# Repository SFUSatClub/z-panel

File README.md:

# Z Face Panel
KiCad project for the outside panel attached to the z faces of the cubesat. The panel contains a SMT GPS antenna and 4 sun sensors. The interface is a MCX jack for the GPS and a 14 pin ribbon cable for the sun sensor power and IO.

This repository uses the SFU Satellite Team's KiCad component library as a submodule.
To start working on the repository:

```
1. Open a git shell
2. Navigate to the directory you wish to place the repository inside
3. git clone --recursive "https://github.com/SFUSatClub/z-panel.git"
```

If you modify either the component schematic or footprint libraries you must push those changes to the SFUSatClub/KiCad-Lib repository, then commit the project repository.

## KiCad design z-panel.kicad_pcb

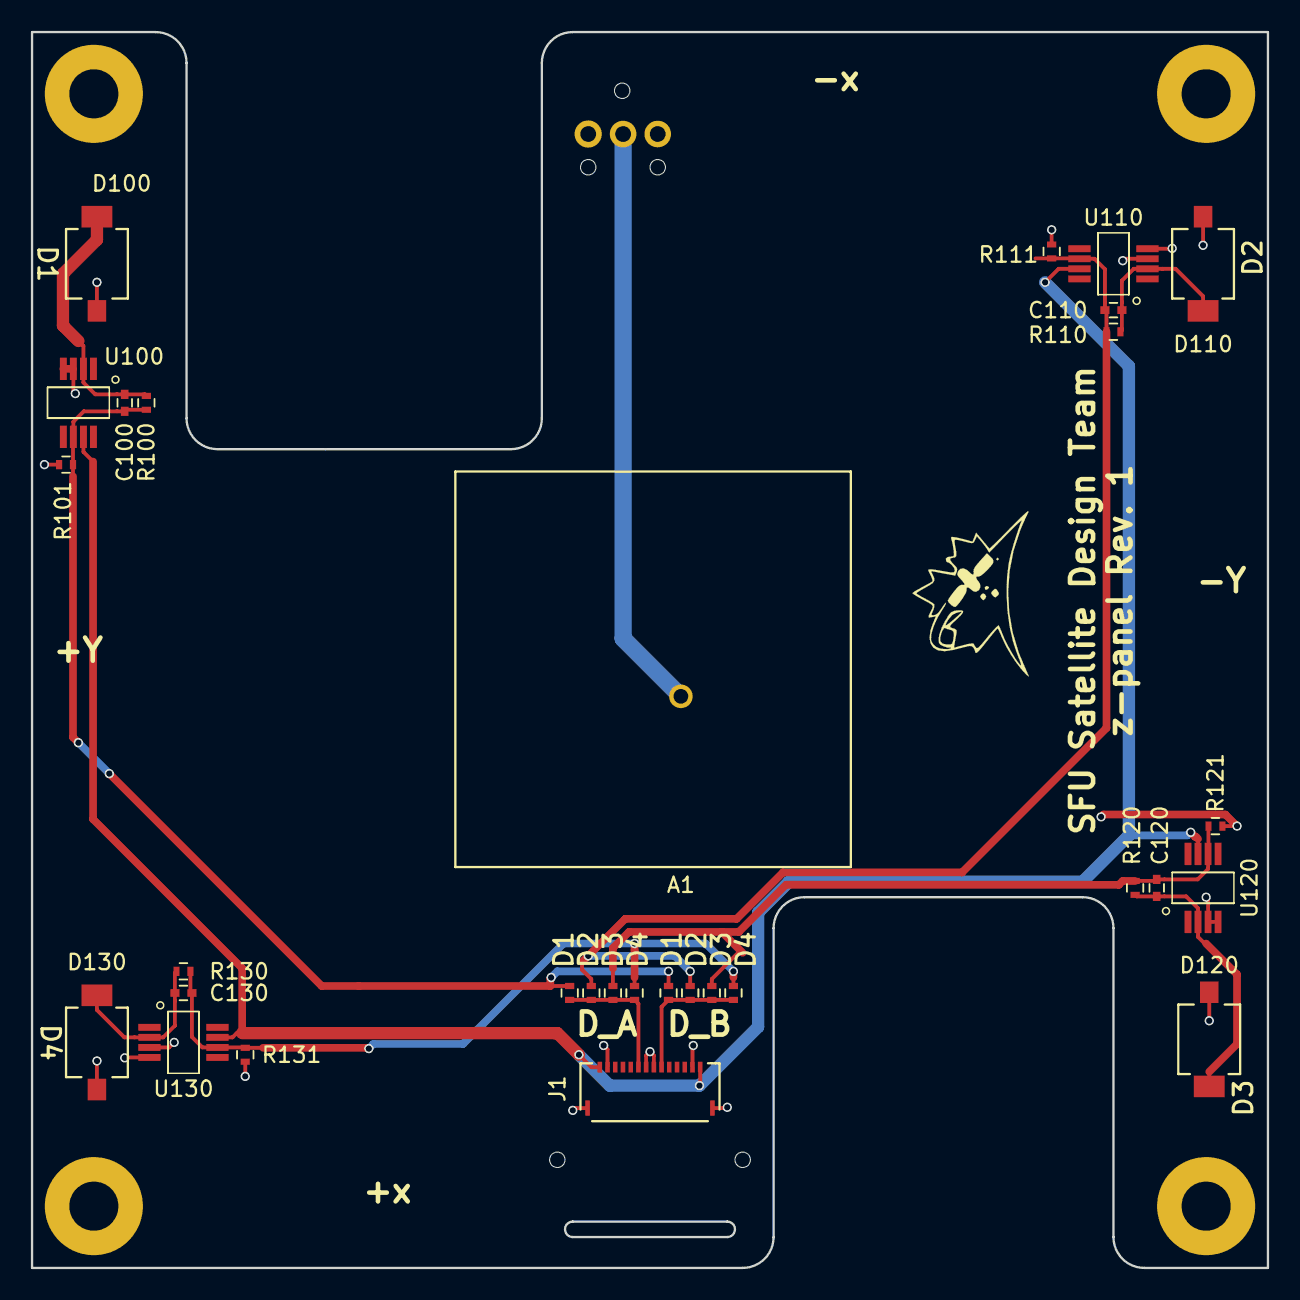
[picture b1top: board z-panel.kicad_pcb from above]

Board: 2 copper layers, 80.0 x 80.0 mm, 37 parts (1 on the bottom side), 13 nets.

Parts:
A1: GPS_ANTENNA; GPS_ANT_4mm
C100, C110, C120, C130: 0.1uF; C_0402
D100, D110, D120, D130: D_Photo; SFH2430
J1: MOLEX_FFC-14
J2, J3, J4, J5: PC104PTH
J6: TEST_1P; vis-0.6mm
J7, J8: TEST_1P; via-0.97mm
R1, R2, R3, R4, R5, R6, R7, R8: 0R; R_0402
R100, R110, R120, R130: 2K2; R_0402
R101, R111, R121, R131: DNP; R_0402
U100, U110, U120, U130: OPA380; VSSOP_8

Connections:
/3V3: J1.1, J1.14, U100.7, U110.7, U120.7, U130.7
/D1: C100.1, R1.1, R2.1, R100.1, R101.1, U100.6
/D2: C110.1, R3.1, R4.1, R110.1, R111.1, U110.6
/D3: C120.1, R5.1, R6.1, R120.1, R121.1, U120.6
/D4: C130.1, R7.1, R8.1, R130.1, R131.1, U130.6
/D_A: J1.6, R1.2, R3.2, R5.2, R7.2
/D_B: J1.9, R2.2, R4.2, R6.2, R8.2
GND: D100.2, D110.2, D120.2, D130.2, J1.2, J1.7, J1.8, J1.13, J1.SHLD, J2.1, J3.1, J4.1, J5.1, J7.1, J8.1, R101.2, R111.2, R121.2, R131.2, U100.3, U100.4, U110.3, U110.4, U120.3, U120.4, U130.3, U130.4
unnamed: A1.1, J6.1
unnamed: C100.2, D100.1, R100.2, U100.2
unnamed: C110.2, D110.1, R110.2, U110.2
unnamed: C120.2, D120.1, R120.2, U120.2
unnamed: C130.2, D130.1, R130.2, U130.2

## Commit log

2018-02-25 added 3d model for photodiode
2018-03-04 layout complete
2018-03-22 added slots for coax access and adjusted FFC position
2018-03-22 added coordinates to silkscreen
2018-03-22 added production doc
2018-03-31 fixed GPS coax entry. Closes #1
2018-04-21 solder mask fixed to conform to min 150um webbing requirement
2018-04-23 generated gerbers
2018-06-02 made schematic
